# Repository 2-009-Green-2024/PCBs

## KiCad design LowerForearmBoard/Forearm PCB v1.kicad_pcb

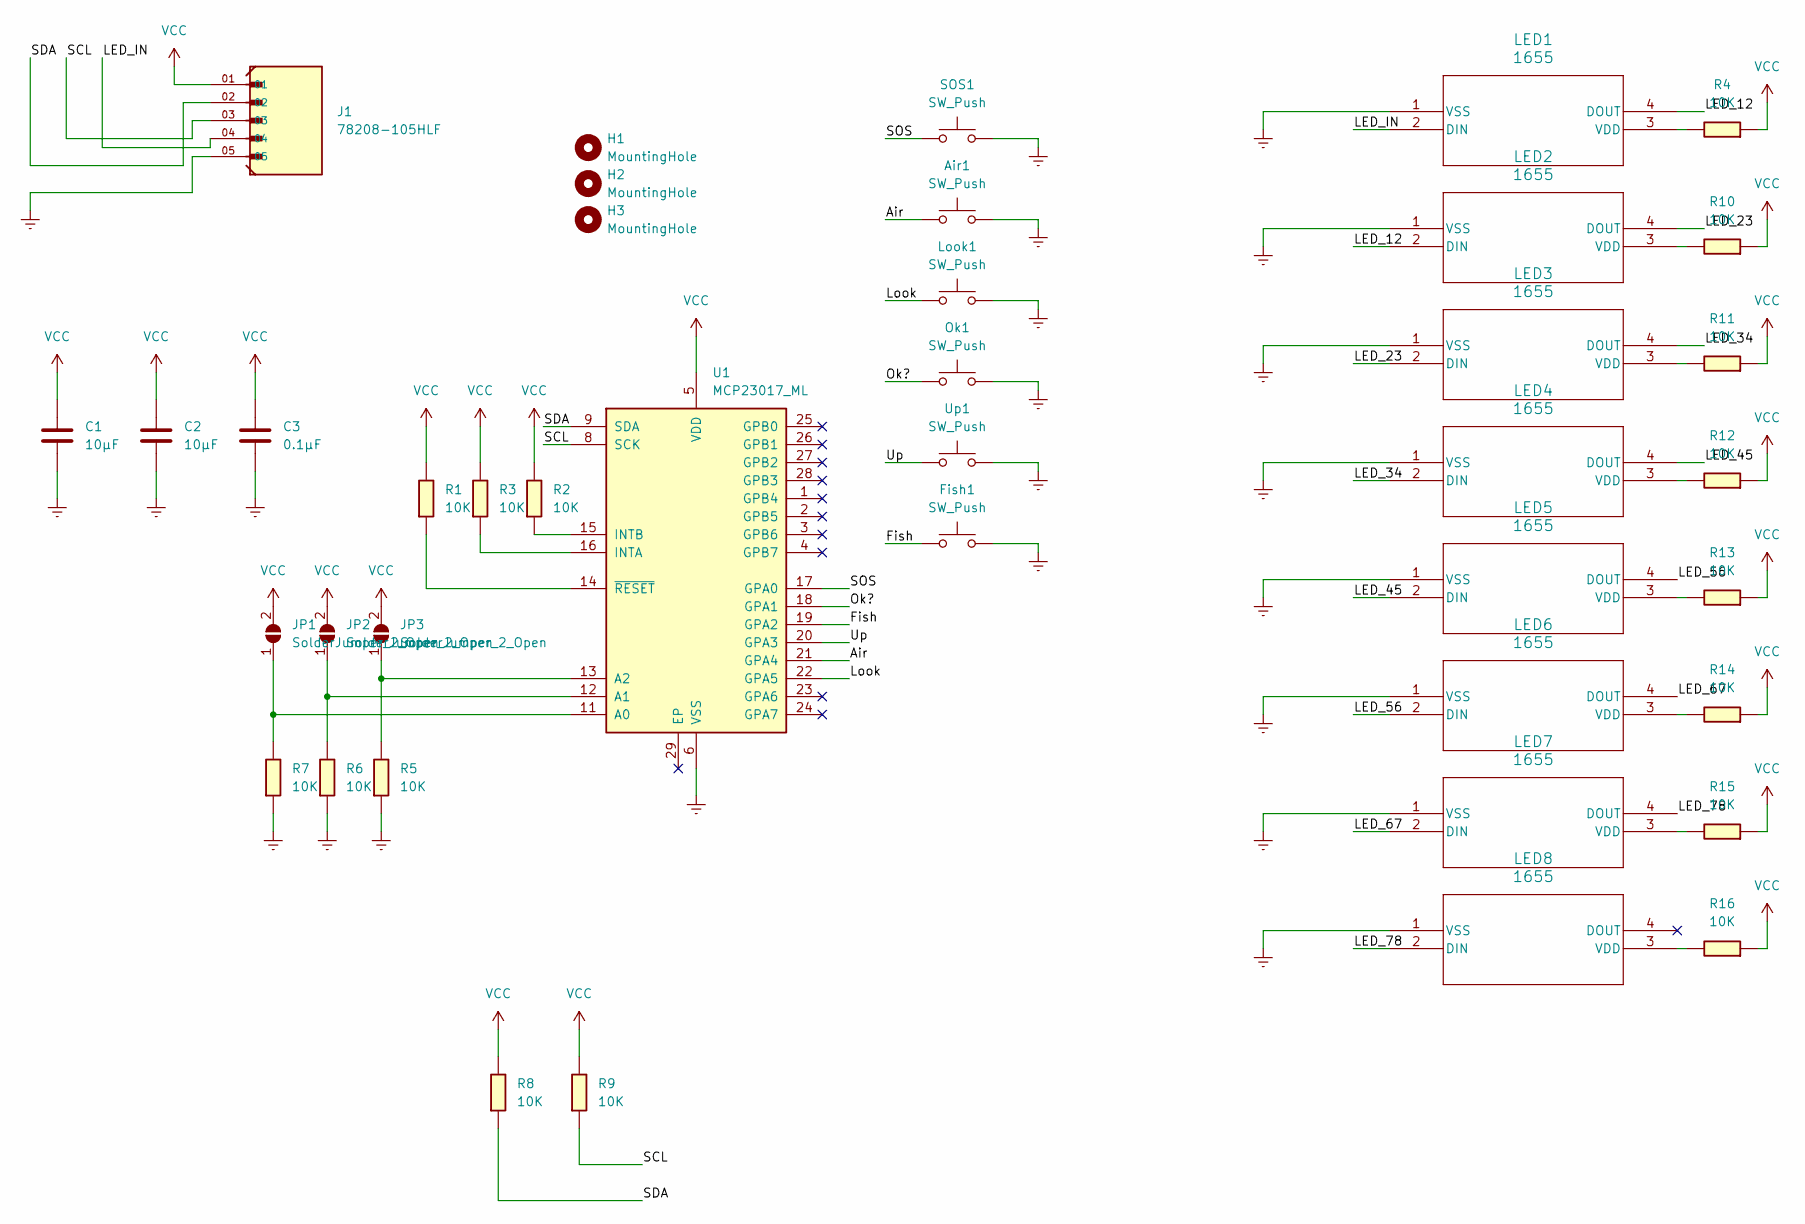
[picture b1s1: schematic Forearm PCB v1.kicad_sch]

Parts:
Air1: SW_Push; SW_TL1107-W_EWI
C1, C2: 10μF; C_0805_2012Metric_Pad1.18x1.45mm_HandSolder
C3: 0.1μF; C_0805_2012Metric_Pad1.18x1.45mm_HandSolder
Fish1: SW_Push; SW_TL1107-W_EWI
H1, H2, H3: MountingHole; MountingHole_2.7mm_M2.5
J1: 78208-105HLF; AMPHENOL_78208-105HLF; PARTREV N
JP1, JP2, JP3: SolderJumper_2_Open; SolderJumper-2_P1.3mm_Bridged2Bar_Pad1.0x1.5mm
LED1, LED2, LED3, LED4, LED5, LED6, LED7, LED8: 1655; Adafruit-1655-0-0-0
Look1: SW_Push; SW_TL1107-W_EWI
Ok1: SW_Push; SW_TL1107-W_EWI
R1, R2, R3, R4, R5, R6, R7, R8, R9, R10, R11, R12, R13, R14, R15, R16: 10K; R_0805_2012Metric_Pad1.20x1.40mm_HandSolder
SOS1: SW_Push; SW_TL1107-W_EWI
U1: MCP23017_ML; QFN-28-1EP_6x6mm_P0.65mm_EP4.25x4.25mm
Up1: SW_Push; SW_TL1107-W_EWI

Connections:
/Air: Air1.1, U1.21 (GPA4)
/Fish: Fish1.1, U1.19 (GPA2)
/LED_12: LED1.4 (DOUT), LED2.2 (DIN)
/LED_23: LED2.4 (DOUT), LED3.2 (DIN)
/LED_34: LED3.4 (DOUT), LED4.2 (DIN)
/LED_45: LED4.4 (DOUT), LED5.2 (DIN)
/LED_56: LED5.4 (DOUT), LED6.2 (DIN)
/LED_67: LED6.4 (DOUT), LED7.2 (DIN)
/LED_78: LED7.4 (DOUT), LED8.2 (DIN)
/LED_IN: J1.04, LED1.2 (DIN)
/Look: Look1.1, U1.22 (GPA5)
/Ok?: Ok1.1, U1.18 (GPA1)
/SCL: J1.03, R9.2, U1.8 (SCK)
/SDA: J1.02, R8.2, U1.9 (SDA)
/SOS: SOS1.1, U1.17 (GPA0)
/Up: U1.20 (GPA3), Up1.1
Earth: Air1.2, C1.2, C2.2, C3.2, Fish1.2, J1.05, LED1.1 (VSS), LED2.1 (VSS), LED3.1 (VSS), LED4.1 (VSS), LED5.1 (VSS), LED6.1 (VSS), LED7.1 (VSS), LED8.1 (VSS), Look1.2, Ok1.2, R5.2, R6.2, R7.2, SOS1.2, U1.6 (VSS), Up1.2
unnamed: JP1.1 (A), R7.1, U1.11 (A0)
unnamed: JP2.1 (A), R6.1, U1.12 (A1)
unnamed: JP3.1 (A), R5.1, U1.13 (A2)
unnamed: LED1.3 (VDD), R4.1
unnamed: LED2.3 (VDD), R10.1
unnamed: LED3.3 (VDD), R11.1
unnamed: LED4.3 (VDD), R12.1
unnamed: LED5.3 (VDD), R13.1
unnamed: LED6.3 (VDD), R14.1
unnamed: LED7.3 (VDD), R15.1
unnamed: LED8.3 (VDD), R16.1
unnamed: R3.2, U1.16 (INTA)
unnamed: R2.2, U1.15 (INTB)
unnamed: R1.2, U1.14 (~RESET)
VCC: C1.1, C2.1, C3.1, J1.01, JP1.2 (B), JP2.2 (B), JP3.2 (B), R1.1, R2.1, R3.1, R4.2, R8.1, R9.1, R10.2, R11.2, R12.2, R13.2, R14.2, R15.2, R16.2, U1.5 (VDD)

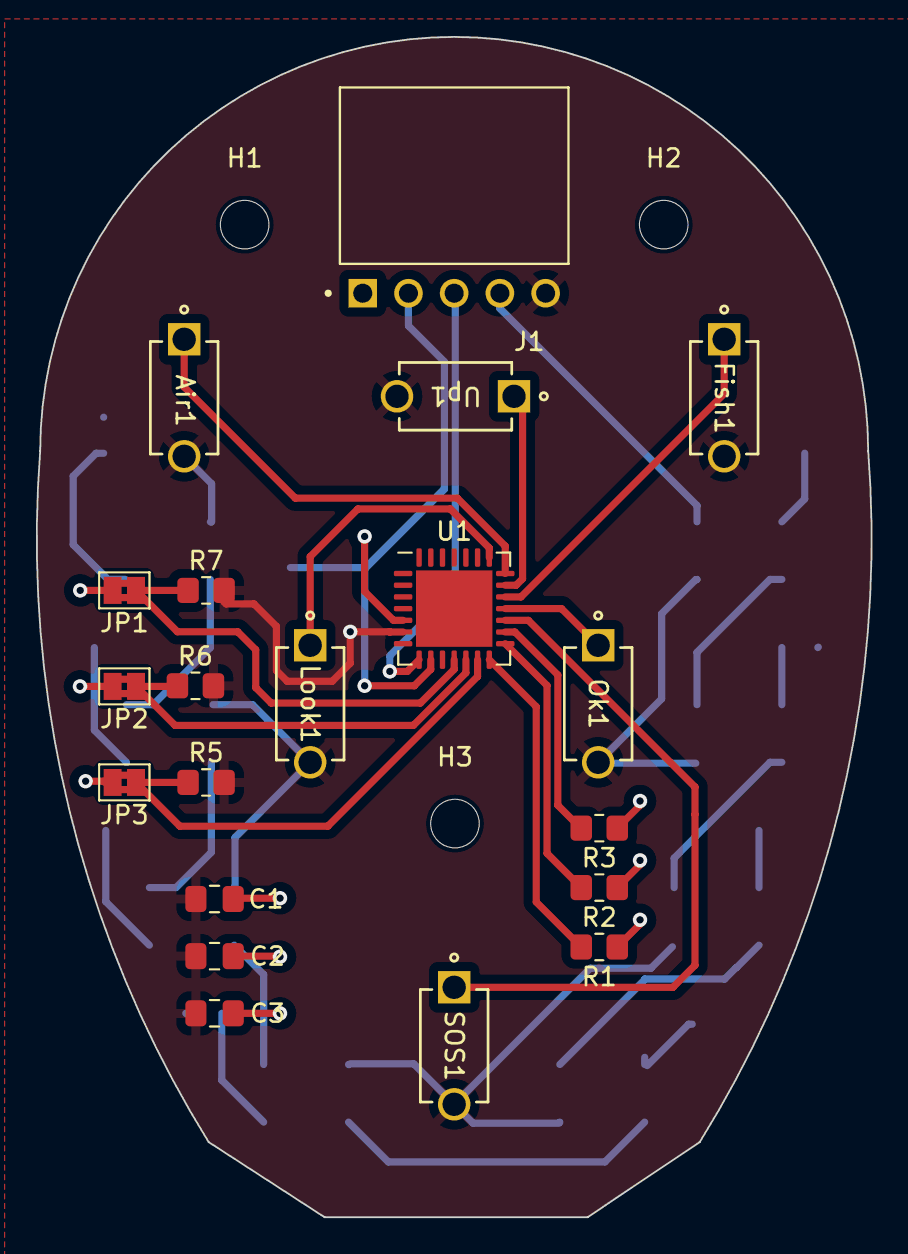
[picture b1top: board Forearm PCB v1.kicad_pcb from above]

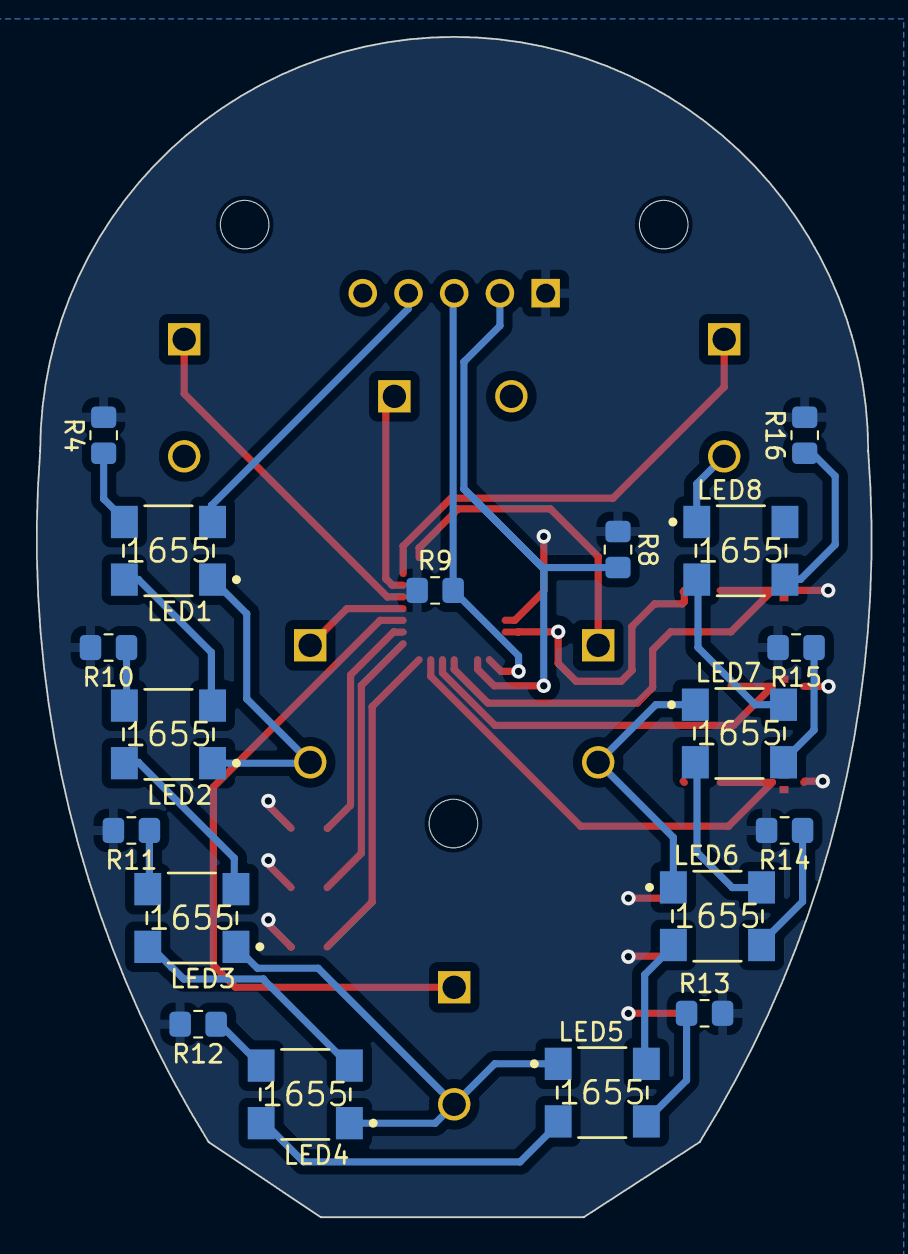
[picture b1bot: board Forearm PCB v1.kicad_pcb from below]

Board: 2 copper layers, 46.4 x 65.6 mm, 41 parts (18 on the bottom side), 32 nets.

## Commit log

2024-11-22 initial fials and dirstructs
2024-11-22 lower board
2024-11-22 initial push of pcb files
2024-11-23 more changes!
2024-11-24 nearly done!
2024-11-27 done upper arm!!
2025-04-05 updated final BRD
